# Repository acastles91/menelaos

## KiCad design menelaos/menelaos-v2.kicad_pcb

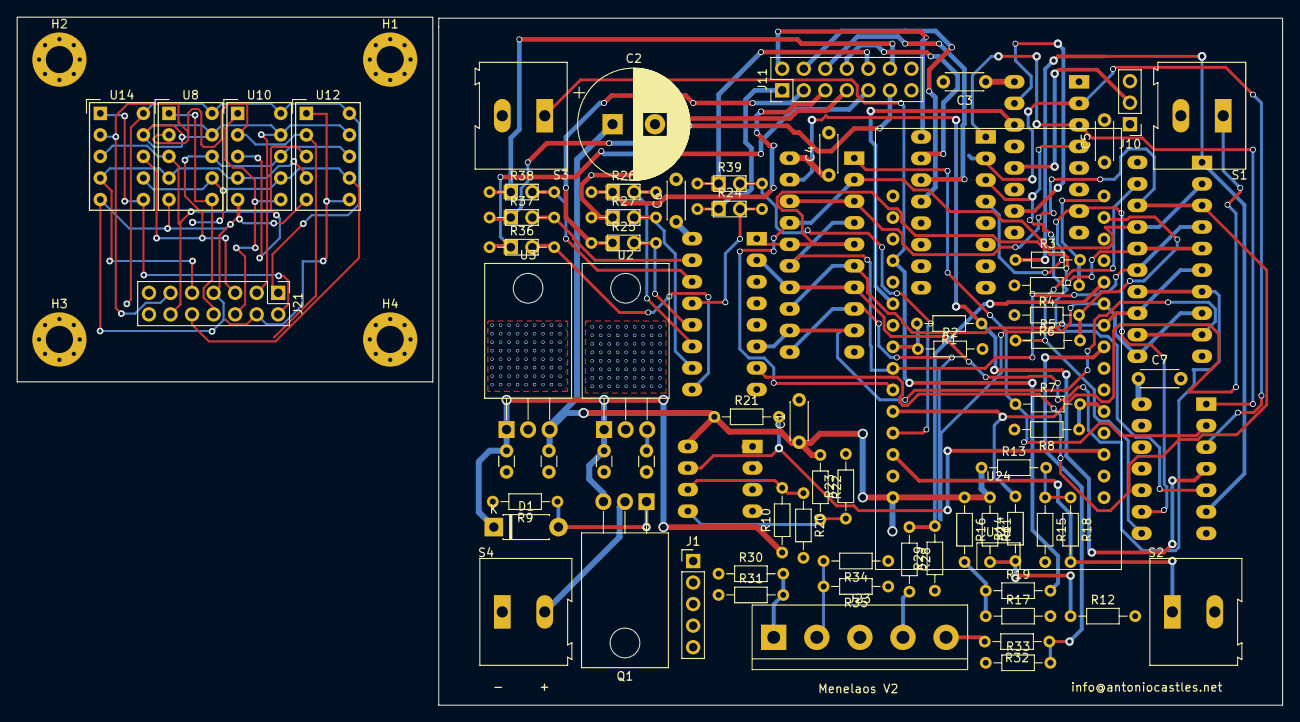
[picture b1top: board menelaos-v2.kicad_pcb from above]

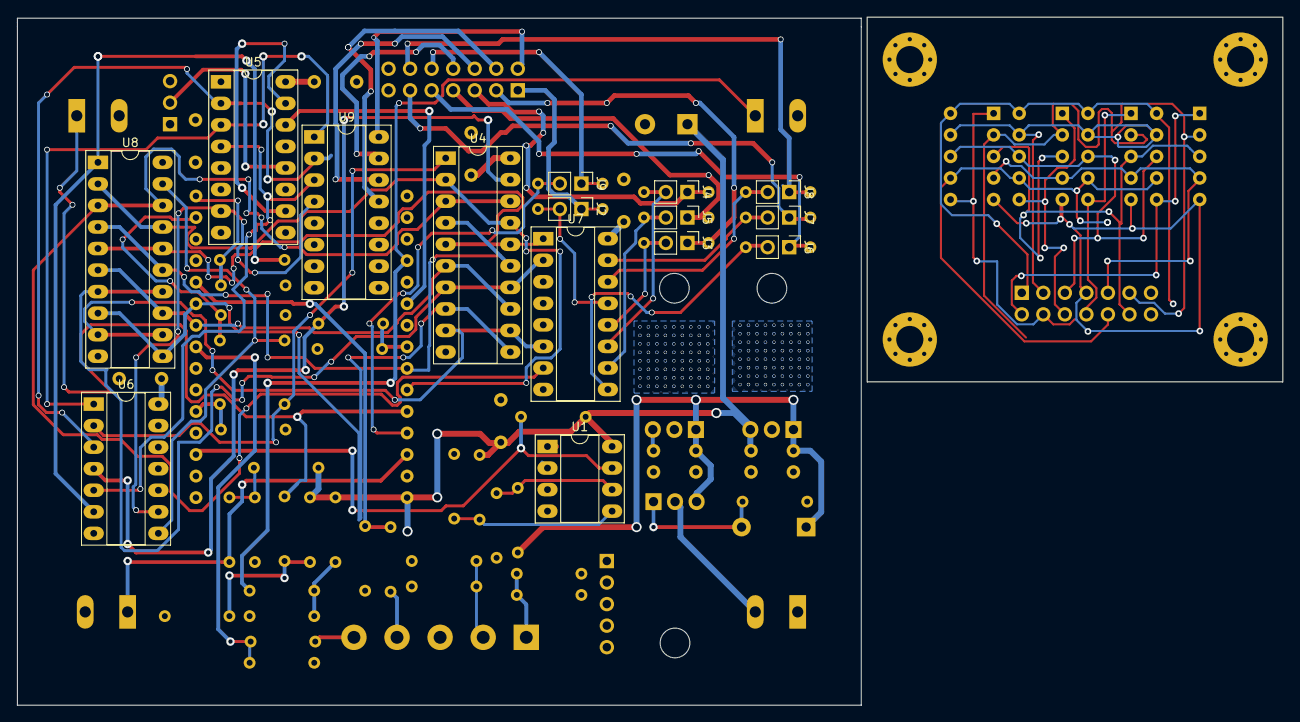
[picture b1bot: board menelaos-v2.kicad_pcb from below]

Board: 4 copper layers, 149.2 x 81.1 mm, 87 parts (15 on the bottom side), 64 nets.

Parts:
C1, C3, C4, C5, C6, C7: C; C_Disc_D4.3mm_W1.9mm_P5.00mm
C2: CP1; CP_Radial_D13.0mm_P5.00mm
D1: D_Zener-10V; D_DO-41_SOD81_P7.62mm_Horizontal
H1, H2, H3, H4: MountingHole; MountingHole_3.2mm_M3_Pad_Via
J1: Conn_01x05_Male; PinHeader_1x05_P2.54mm_Vertical
J2, J3, J4, J5, J6, J7, J8, J9: Conn_01x02_Male; PinHeader_1x02_P2.54mm_Vertical
J10: Conn_01x03_Male; PinHeader_1x03_P2.54mm_Vertical
J11, J21: Conn_02x07_Counter_Clockwise; PinHeader_2x07_P2.54mm_Vertical-counterclockwise
J23: DIN-5-TerminalBlock; TerminalBlock_bornier-5_P5.08mm
Murata-Ceramic-Capacitor-50v1-22uF1, Murata-Ceramic-Capacitor-50v1-22uF2, Murata-Ceramic-Capacitor-50v1-22uF3, Murata-Ceramic-Capacitor-50v1-22uF4: C; C_Disc_D3.0mm_W1.6mm_P2.50mm
Q1: IRF5305-Reverse-Polarity; TO-220-3_Horizontal_TabDown
R1, R3, R5, R7, R11, R13, R16: 5K; R_Axial_DIN0204_L3.6mm_D1.6mm_P7.62mm_Horizontal
R2, R4, R6, R8, R12, R14, R15, R17, R18, R19: 10K; R_Axial_DIN0204_L3.6mm_D1.6mm_P7.62mm_Horizontal
R9: 100K; R_Axial_DIN0204_L3.6mm_D1.6mm_P7.62mm_Horizontal
R10, R20, R21, R22, R23, R24, R25, R26, R27, R36, R37, R38, R39: R; R_Axial_DIN0204_L3.6mm_D1.6mm_P7.62mm_Horizontal
R28, R32: 50; R_Axial_DIN0204_L3.6mm_D1.6mm_P7.62mm_Horizontal
R29, R30, R33, R34: 220; R_Axial_DIN0204_L3.6mm_D1.6mm_P7.62mm_Horizontal
R31, R35: 100; R_Axial_DIN0204_L3.6mm_D1.6mm_P7.62mm_Horizontal
S1, S2, S3, S4: Generic-Switch; TerminalBlock_Altech_AK300-2_P5.00mm
U1: LM393; DIP-8_W7.62mm_Socket_LongPads
U2, U3: L7805; TO-220-3_Horizontal_TabDown
U4, U8#2: 74HCT244; DIP-20_W7.62mm_Socket_LongPads
U5: 74HC4017E; DIP-16_W7.62mm_Socket_LongPads
U6: 74HC04; DIP-14_W7.62mm_Socket_LongPads
U7: 74HC4511E; DIP-16_W7.62mm_Socket_LongPads
U8, U10, U12, U14: HDSP-7503; HDSP-A151
U9: ULN2003; DIP-16_W7.62mm_Socket_LongPads
U24: ESP32-WROOM-32D; ESP32-DEVKIT

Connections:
+5VL: C1.1, C2.1, Murata-Ceramic-Capacitor-50v1-22uF4.1, R11.1, R13.1, R16.1, R21.1, R22.1, U1.8, U3.3, U24.15
+12V: D1.1, Murata-Ceramic-Capacitor-50v1-22uF1.1, Murata-Ceramic-Capacitor-50v1-22uF2.1, Q1.3, R10.1, U2.1, U3.1
/7-segmet-display/BCD_out1: U4.3, U4.18, U7.7, U8#2.3, U8#2.18
/7-segmet-display/BCD_out2: U4.5, U4.16, U7.1, U8#2.5, U8#2.16
/7-segmet-display/BCD_out3: U4.7, U4.14, U7.2, U8#2.7, U8#2.14
/7-segmet-display/BCD_out4: U4.9, U4.12, U7.6, U8#2.9, U8#2.12
GND: C1.2, C2.2, C3.2, C4.2, C5.2, C6.2, C7.2, J1.1, J1.2, J1.3, J1.4, J1.5, J10.3, Murata-Ceramic-Capacitor-50v1-22uF1.2, Murata-Ceramic-Capacitor-50v1-22uF2.2, Murata-Ceramic-Capacitor-50v1-22uF3.2, Murata-Ceramic-Capacitor-50v1-22uF4.2, R2.2, R4.2, R6.2, R8.2, R9.2, R12.2, R15.2, R17.2, R20.2, R23.2, R29.1, R30.1, R31.1, R33.1, R34.1, R35.1, S1.2, S2.2, S3.2, S4.1, U1.4, U2.2, U3.2, U4.10, U5.8, U5.13, U6.7, U7.5, U7.8, U8#2.10, U9.8, U24.14, U24.17
unnamed: D1.2, Q1.1, R9.1
unnamed: J10.2, U5.12
unnamed: Q1.2, S4.2
unnamed: R10.2, R20.1, U1.6
unnamed: R11.2, R12.1, R14.1
unnamed: R13.2, R15.1, R18.1
unnamed: R16.2, R17.1, R19.1
unnamed: R22.2, R23.1, U1.5
unnamed: U5.2, U6.3, U9.2
unnamed: U5.3, U6.1, U9.1
unnamed: U5.4, U6.5, U9.3
unnamed: U5.7, U6.9, U9.4
unnamed: U5.10, U5.15
_a: J2.1, J11.1, R24.1
_a1: U4.2, U4.17, U8#2.2, U8#2.17, U24.10
_a2: U4.4, U4.15, U8#2.4, U8#2.15, U24.9
_a3: U4.6, U4.13, U8#2.6, U8#2.13, U24.24
_a4: U4.8, U4.11, U8#2.8, U8#2.11, U24.25
_b: J3.1, J11.2, R25.1
_c: J4.1, J11.3, R26.1
_chA: R28.1, R29.2, U24.26
_chB: R32.1, R33.2, U24.23
_clk: U5.14, U24.6
_config: R19.2, S3.1, U24.4
_d: J5.1, J11.4, R27.1
_dp: J9.1, J11.10, R39.1
_dpBoard: J9.2, R39.2, U24.12
_e: J6.1, J11.5, R36.1
_f: J7.1, J11.6, R37.1
_g: J8.1, J11.9, R38.1
_hundreds: R5.1, U6.8, U8#2.19
_hundredsBoard: R5.2, R6.1, U24.29
_mode: R18.2, S2.1, U24.13
_ones: R1.1, U4.19, U6.4
_onesBoard: R1.2, R2.1, U24.8
_save: R21.2, U1.7, U24.18
_tens: R3.1, U6.6, U8#2.1
_tensBoard: R3.2, R4.1, U24.30
_thousands: R7.1, U4.1, U6.2
_thousandsBoard: R7.2, R8.1, U24.20
_zero: R14.2, S1.1, U24.11
a: J2.2, R24.2, U7.13
b: J3.2, R25.2, U7.12
black: J23.5, R32.2
blue: C3.1, C4.1, C5.1, C6.1, C7.1, J10.1, J23.3, Murata-Ceramic-Capacitor-50v1-22uF3.1, U2.3, U4.20, U5.16, U6.14, U7.3, U7.4, U7.16, U8#2.20
c: J4.2, R26.2, U7.11
d: J5.2, R27.2, U7.10
e: J6.2, R36.2, U7.9
f: J7.2, R37.2, U7.15
g: J8.2, R38.2, U7.14
hundreds: J11.13, U9.13
ones: J11.11, U9.15
red: J23.1, R30.2, R31.2
tens: J11.12, U9.14
thousands: J11.14, U9.16
white: J23.2, R34.2, R35.2
yellow: J23.4, R28.2

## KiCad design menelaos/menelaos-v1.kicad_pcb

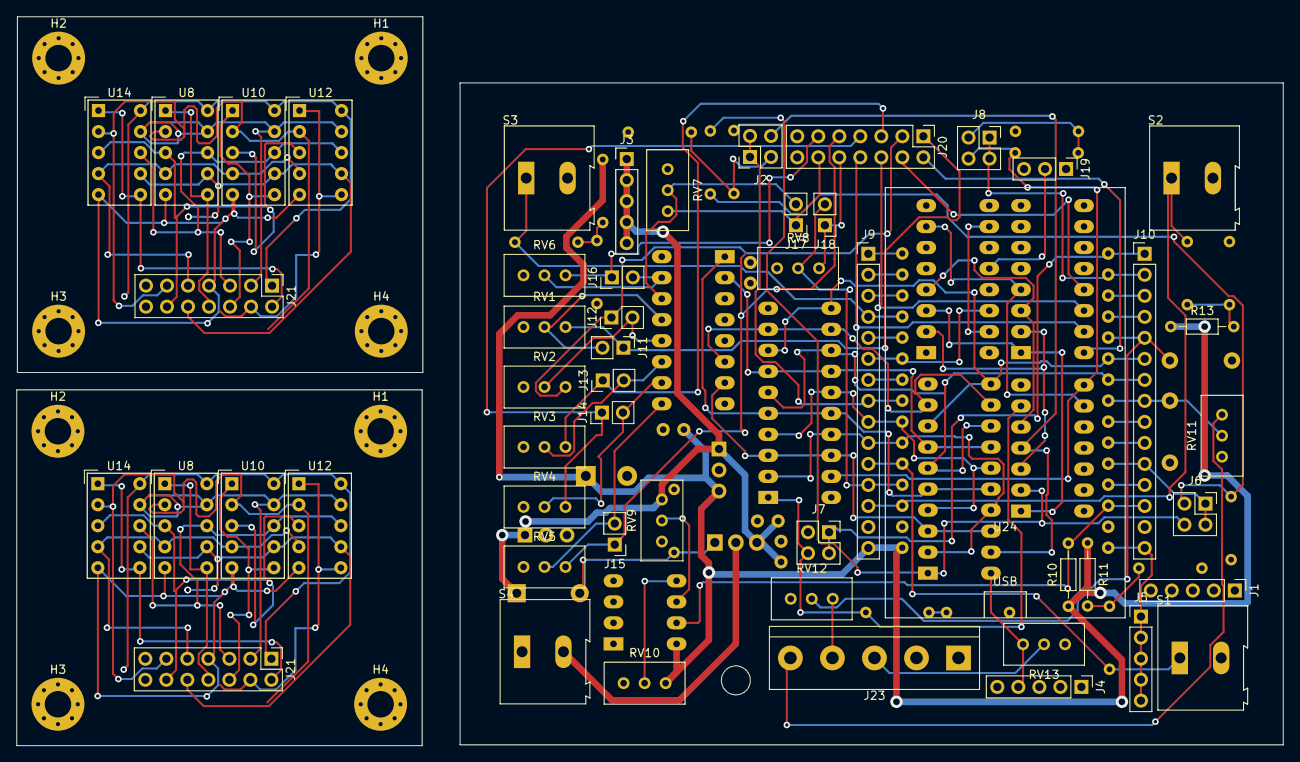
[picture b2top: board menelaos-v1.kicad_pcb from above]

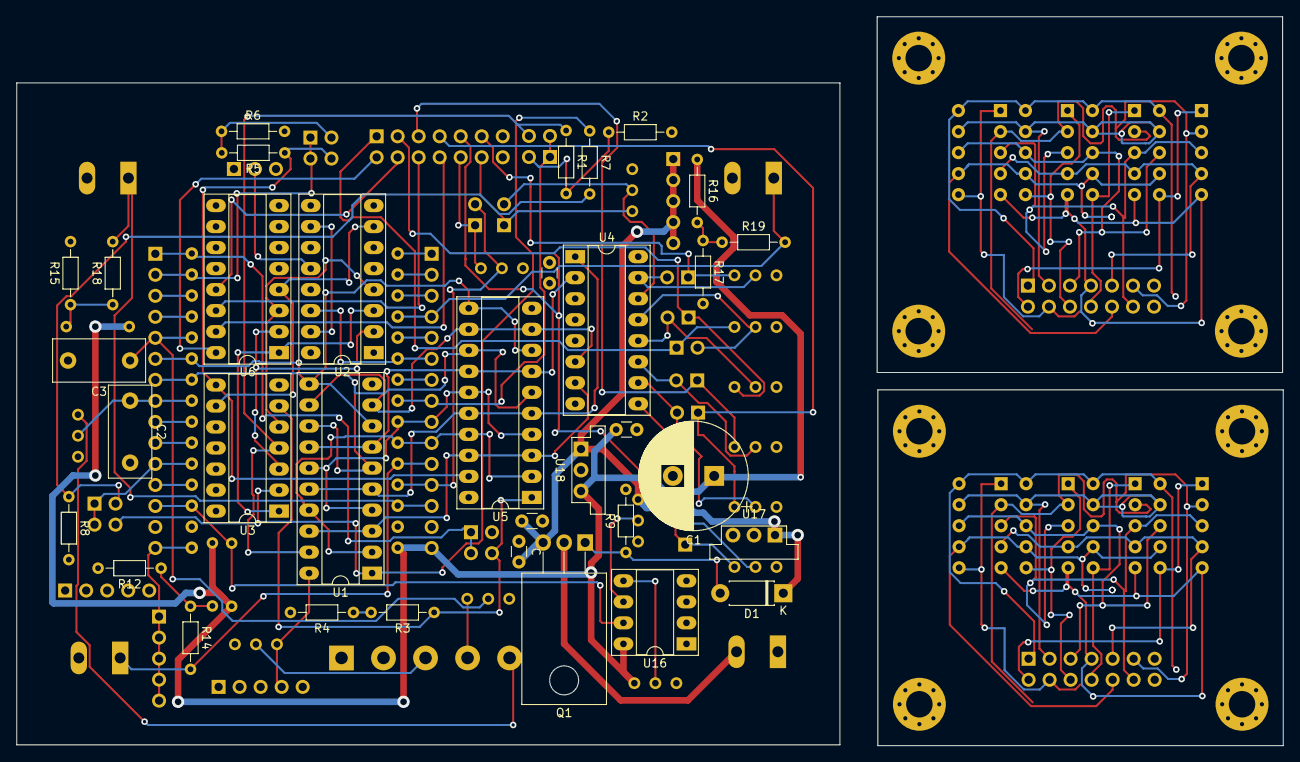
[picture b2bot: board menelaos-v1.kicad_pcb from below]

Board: 4 copper layers, 99.5 x 80.0 mm, 94 parts (34 on the bottom side), 90 nets.

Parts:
C1: CP1; CP_Radial_D13.0mm_P5.00mm
C2, C3: C; C_Disc_D11.0mm_W5.0mm_P7.50mm
D1: D_Zener-10V; D_DO-41_SOD81_P7.62mm_Horizontal
H1, H1#2, H2, H2#2, H3, H3#2, H4, H4#2: MountingHole; MountingHole_3.2mm_M3_Pad_Via
J1, J3, J4, J5: Conn_01x05_Male; PinHeader_1x05_P2.54mm_Vertical
J2, J6, J7, J8: Conn_02x02_Counter_Clockwise; PinSocket_2x02_P2.54mm_Vertical_CounterClockWise
J9, J10: Conn_01x15_Male; PinHeader_1x15_P2.54mm_Vertical
J11, J12, J13, J14, J15, J16, J17, J18: Conn_01x02_Male; PinHeader_1x02_P2.54mm_Vertical
J19: Conn_01x03_Male; PinHeader_1x03_P2.54mm_Vertical
J20, J21, J21#2: Conn_02x07_Counter_Clockwise; PinHeader_2x07_P2.54mm_Vertical-counterclockwise
J23: DIN-5-TerminalBlock; TerminalBlock_bornier-5_P5.08mm
Murata-Ceramic-Capacitor-50v1-22uF1, Murata-Ceramic-Capacitor-50v1-22uF2, Murata-Ceramic-Capacitor-50v1-22uF3, Murata-Ceramic-Capacitor-50v1-22uF4: C; C_Disc_D3.0mm_W1.6mm_P2.50mm
Q1: IRF5305-Reverse-Polarity; TO-220-3_Horizontal_TabDown
R1, R3, R5, R7, R11, R13, R16: 5K; R_Axial_DIN0204_L3.6mm_D1.6mm_P7.62mm_Horizontal
R2, R4, R6, R8, R12, R14, R15, R17, R18, R19: 10K; R_Axial_DIN0204_L3.6mm_D1.6mm_P7.62mm_Horizontal
R9: 100K; R_Axial_DIN0204_L3.6mm_D1.6mm_P7.62mm_Horizontal
R10: R; R_Axial_DIN0204_L3.6mm_D1.6mm_P7.62mm_Horizontal
RV1, RV2, RV3, RV4, RV5, RV6, RV7, RV8, RV9, RV10, RV11, RV12, RV13: R_POT_TRIM; Potentiometer_Bourns_3296W_Vertical
S1, S2, S3, S4: Generic-Switch; TerminalBlock_Altech_AK300-2_P5.00mm
U1, U5: 74HCT244; DIP-20_W7.62mm_Socket_LongPads
U2: 74HC4017E; DIP-16_W7.62mm_Socket_LongPads
U3: 74HC04; DIP-14_W7.62mm_Socket_LongPads
U4: 74HC4511E; DIP-16_W7.62mm_Socket_LongPads
U6: ULN2003; DIP-16_W7.62mm_Socket_LongPads
U8, U8#2, U10, U10#2, U12, U12#2, U14, U14#2: HDSP-7503; HDSP-A151
U16: LM393; DIP-8_W7.62mm_Socket_LongPads
U17, U18: OKI-78SR-5v; Converter_DCDC_muRata_OKI-78SR_Vertical
U24: ESP32-WROOM-32D; ESP32-DEVKIT

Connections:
+3V3: J5.1, J5.2, J5.3, J5.4, J5.5, J10.15, U24.16
+5VL: C1.1, J9.15, Murata-Ceramic-Capacitor-50v1-22uF4.1, R10.1, R11.1, R13.1, R16.1, RV10.1, U16.8, U18.3, U24.15
+5VP: J4.1, J4.2, J4.3, J4.4, J4.5, J19.1, Murata-Ceramic-Capacitor-50v1-22uF3.1, RV13.1, U1.20, U2.16, U3.14, U4.3, U4.4, U4.16, U5.20, U17.3
+12V: D1.1, J3.1, J3.2, J3.3, J3.4, J3.5, Murata-Ceramic-Capacitor-50v1-22uF1.1, Murata-Ceramic-Capacitor-50v1-22uF2.1, Q1.3, RV9.1, U17.1, U18.1
+a: J21#2.1, U8#2.10, U10#2.10, U12#2.10, U14#2.10
+b: J21#2.2, U8#2.9, U10#2.9, U12#2.9, U14#2.9
+c: J21#2.3, U8#2.8, U10#2.8, U12#2.8, U14#2.8
+d: J21#2.4, U8#2.5, U10#2.5, U12#2.5, U14#2.5
+dp: J21#2.10, U8#2.7, U10#2.7, U12#2.7, U14#2.7
+e: J21#2.5, U8#2.4, U10#2.4, U12#2.4, U14#2.4
+f: J21#2.6, U8#2.2, U10#2.2, U12#2.2, U14#2.2
+g: J21#2.9, U8#2.3, U10#2.3, U12#2.3, U14#2.3
+hundreds: J21#2.13, U12#2.1, U12#2.6
+ones: J21#2.11, U8#2.1, U8#2.6
+tens: J21#2.12, U10#2.1, U10#2.6
+thousands: J21#2.14, U14#2.1, U14#2.6
/7-segmet-display/BCD_out1: U1.3, U1.18, U4.7, U5.3, U5.18
/7-segmet-display/BCD_out2: U1.5, U1.16, U4.1, U5.5, U5.16
/7-segmet-display/BCD_out3: U1.7, U1.14, U4.2, U5.7, U5.14
/7-segmet-display/BCD_out4: U1.9, U1.12, U4.6, U5.9, U5.12
unnamed: D1.2, Q1.1, R9.1
unnamed: J9.1, U24.1
unnamed: J9.2, U24.2
unnamed: J9.3, U24.3
unnamed: J9.5, U24.5
unnamed: J9.7, U24.7
unnamed: J10.3, U24.28
unnamed: J10.4, U24.27
unnamed: J10.9, U24.22
unnamed: J10.10, U24.21
unnamed: J10.12, U24.19
unnamed: J19.2, U2.12
unnamed: R11.2, R12.1, R14.1
unnamed: R13.2, R15.1, R18.1
unnamed: R16.2, R17.1, R19.1
unnamed: RV9.2, U16.6
unnamed: RV10.2, U16.5
unnamed: U2.2, U3.3, U6.2
unnamed: U2.3, U3.1, U6.1
unnamed: U2.4, U3.5, U6.3
unnamed: U2.7, U3.9, U6.4
unnamed: U2.10, U2.15
POWER-IN+: Q1.2, S4.2
POWER-IN-: C1.2, C2.2, C3.2, J1.1, J1.2, J1.3, J1.4, J1.5, J9.14, J10.14, J19.3, J23.1, J23.2, Murata-Ceramic-Capacitor-50v1-22uF1.2, Murata-Ceramic-Capacitor-50v1-22uF2.2, Murata-Ceramic-Capacitor-50v1-22uF3.2, Murata-Ceramic-Capacitor-50v1-22uF4.2, R2.2, R4.2, R6.2, R8.2, R9.2, R12.2, R15.2, R17.2, RV1.3, RV2.3, RV3.3, RV4.3, RV5.3, RV6.3, RV7.3, RV8.3, RV9.3, RV10.3, RV11.3, RV12.3, RV13.3, S1.2, S2.2, S3.2, S4.1, U1.10, U2.8, U2.13, U3.7, U4.5, U4.8, U5.10, U6.8, U16.4, U17.2, U18.2, U24.14, U24.17
_a: J11.1, J20.1, RV1.1
_a1: J9.10, U1.2, U1.17, U5.2, U5.17, U24.10
_a2: J9.9, U1.4, U1.15, U5.4, U5.15, U24.9
_a3: J10.7, U1.6, U1.13, U5.6, U5.13, U24.24
_a4: J10.6, U1.8, U1.11, U5.8, U5.11, U24.25
_b: J12.1, J20.2, RV2.1
_c: J13.1, J20.3, RV3.1
_chA: C3.1, J10.5, RV12.2, U24.26
_chB: C2.1, J10.8, RV11.2, U24.23
_clk: J9.6, U2.14, U24.6
_config: J9.4, R19.2, S3.1, U24.4
_d: J14.1, J20.4, RV4.1
_dp: J18.1, J20.10, RV8.1
_dpBoard: J9.12, J18.2, RV8.2, U24.12
_e: J15.1, J20.5, RV5.1
_f: J16.1, J20.6, RV6.1
_g: J17.1, J20.9, RV7.1
_hundreds: J8.2, R5.1, U3.8, U5.19
_hundredsBoard: J8.3, J8.4, J10.2, U24.29
_mode: J9.13, R18.2, S2.1, U24.13
_ones: J2.2, R1.1, U1.19, U3.4
_onesBoard: J2.3, J2.4, J9.8, U24.8
_save: J10.13, R10.2, U16.7, U24.18
_tens: J7.2, R3.1, U3.6, U5.1
_tensBoard: J7.3, J7.4, J10.1, U24.30
_thousands: J6.2, R7.1, U1.1, U3.2
_thousandsBoard: J6.3, J6.4, J10.11, U24.20
_zero: J9.11, R14.2, S1.1, U24.11
a: J11.2, RV1.2, U4.13
b: J12.2, RV2.2, U4.12
c: J13.2, RV3.2, U4.11
d: J14.2, RV4.2, U4.10
e: J15.2, RV5.2, U4.9
f: J16.2, RV6.2, U4.15
g: J17.2, RV7.2, U4.14
gray: J23.5, RV11.1
hundreds: J20.13, U6.13
hundreds33: J8.1, R5.2, R6.1
ones: J20.11, U6.15
ones33: J2.1, R1.2, R2.1
tens: J20.12, U6.14
tens33: R3.2, R4.1
thousands: J20.14, U6.16
thousands33: J6.1, R7.2, R8.1
white: J23.3, RV13.2
yellow: J23.4, RV12.1

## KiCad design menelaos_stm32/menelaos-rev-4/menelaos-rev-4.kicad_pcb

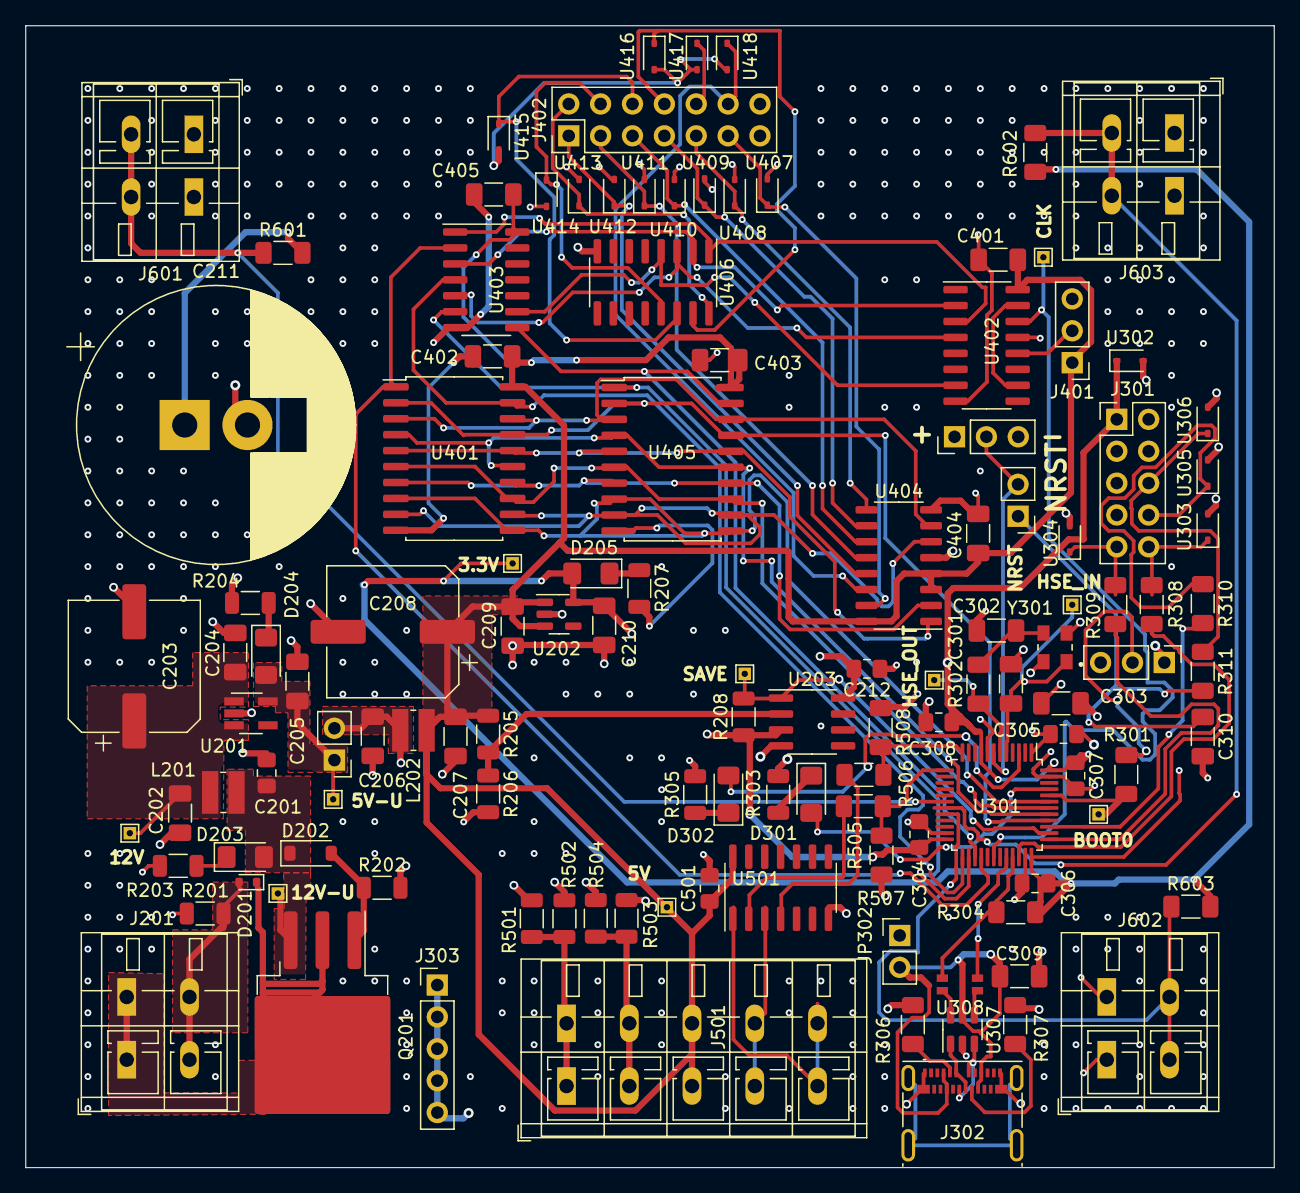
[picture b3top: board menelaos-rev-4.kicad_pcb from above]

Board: 4 copper layers, 99.5 x 91.0 mm, 124 parts (0 on the bottom side), 84 nets.

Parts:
C201, C212: 0.1uF; C_0805_2012Metric_Pad1.18x1.45mm_HandSolder
C202, C205, C206, C207, C404: 0.1uF; C_1206_3216Metric_Pad1.33x1.80mm_HandSolder
C203, C208: C_Polarized; CP_Elec_10x12.6
C204: 0.33uF; C_1206_3216Metric_Pad1.33x1.80mm_HandSolder
C209, C210: 1uF; C_1206_3216Metric_Pad1.33x1.80mm_HandSolder
C211: CP1; CP_Radial_D22.0mm_P5.00mm_SnapIn
C301, C302: 12p; C_1206_3216Metric_Pad1.33x1.80mm_HandSolder
C303: 10u; C_1206_3216Metric_Pad1.33x1.80mm_HandSolder
C304, C305, C306, C307, C308: 100n; C_0805_2012Metric_Pad1.18x1.45mm_HandSolder
C309: 10p; C_1206_3216Metric_Pad1.33x1.80mm_HandSolder
C310: 100n; C_1206_3216Metric_Pad1.33x1.80mm_HandSolder
C401, C402, C403, C405: C; C_1206_3216Metric_Pad1.33x1.80mm_HandSolder
C501: C; C_0805_2012Metric_Pad1.18x1.45mm_HandSolder
D201: ESD5Zxx; D_SOD-523
D202: D_Zener-10V; D_SOD-123
D203, D204, D205, D301, D302: LED; LED_1206_3216Metric_Pad1.42x1.75mm_HandSolder
J201, J601, J602, J603: Screw_Terminal_01x02; TerminalBlock_WAGO_236-402_1x02_P5.00mm_45Degree
J301: Conn_02x05_Counter_Clockwise; PinHeader_2x05_P2.54mm_Vertical
J302: USB_C_Receptacle_USB2.0; USB_C_Receptacle_Molex_105450-0101
J303: Conn_01x05_Male; PinHeader_1x05_P2.54mm_Vertical
J401: Conn_01x03_Male; PinHeader_1x03_P2.54mm_Vertical
J402: Conn_02x07_Counter_Clockwise; PinHeader_2x07_P2.54mm_Vertical-CounterClockWise
J501: DIN-5-TerminalBlock; TerminalBlock_WAGO_236-405_1x05_P5.00mm_45Degree
JP201, JP302: Jumper_2_Open; PinHeader_1x02_P2.54mm_Vertical
JP301, JP304: Jumper_3_Open; PinHeader_1x03_P2.54mm_Vertical
JP303: Jumper_2_Bridged; PinHeader_1x02_P2.54mm_Vertical
L201, L202: L; L_Wuerth_MAPI-3015
Q201: IRF5305-Reverse-Polarity; TO-263-3_TabPin2
R201: 0; R_1206_3216Metric
R202: 100K; R_1206_3216Metric
R203, R204: R_US; R_1206_3216Metric
R205: 5K; R_1206_3216Metric
R206: 10K; R_1206_3216Metric
R207, R303, R305: R100; R_1206_3216Metric
R208: R; R_1206_3216Metric
R301, R505, R506, R507, R508, R601, R602, R603: R10k; R_1206_3216Metric_Pad1.30x1.75mm_HandSolder
R302: R0; R_1206_3216Metric_Pad1.30x1.75mm_HandSolder
R304: R1k5; R_1206_3216Metric_Pad1.30x1.75mm_HandSolder
R306, R307: R5k1; R_1206_3216Metric_Pad1.30x1.75mm_HandSolder
R308, R309, R310, R311: 49R9; R_1206_3216Metric_Pad1.30x1.75mm_HandSolder
R501, R503: 220; R_1206_3216Metric
R502, R504: 100; R_1206_3216Metric
TP201, TP202, TP203, TP204, TP205, TP206, TP301, TP302, TP303, TP401: TestPoint; TestPoint_THTPad_1.0x1.0mm_Drill0.5mm
U201: NCP718-LDO_Regulator; SOT-23-5_HandSoldering
U202: MIC5504-3.3YM5; SOT-23-5
U203: LM2903; SOIC-8_3.9x4.9mm_P1.27mm
U301: STM32F103CBTx; LQFP-48_7x7mm_P0.5mm
U302, U303, U304, U305, U306, U407, U408, U409, U410, U411, U412, U413, U414, U415, U416, U417, U418: PESD3V3L1BA-Bidirectional_Diode; D_SOD-323
U307: USBLC6-2SC6; SOT-23-6
U308: SRF3216A-Common_Mode_Choke; Bourns_SRF3216A
U401, U405: 74HCT244; SOIC-20W_7.5x12.8mm_P1.27mm
U402: 74HC4017E; SOIC-16_3.9x9.9mm_P1.27mm
U403: 74HC04; SOIC-14_3.9x8.7mm_P1.27mm
U404: 74HC4511E; SO-16_3.9x9.9mm_P1.27mm
U406: ULN2003; SOIC-16_3.9x9.9mm_P1.27mm
U501: 74HC14; SOIC-14_3.9x8.7mm_P1.27mm
Y301: CX3225SB16000H0PSTC1-Crystal; OSCCC320X250X60N

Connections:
+3.3V: C210.1, C211.1, C212.2, C303.1, C304.1, C305.1, C306.1, C307.1, C308.1, D205.2 (A), J301.1, JP301.3 (B), JP304.1 (A), R208.1, R304.2, R601.2, R602.2, R603.2, TP206.1, U202.5 (VOUT), U203.3 (+), U203.8 (V+), U301.1 (VBAT), U301.9 (VDDA), U301.24 (VDD), U301.36 (VDD), U301.48 (VDD), U302.1
+12V: C202.1, C203.1, C204.1, L201.2, TP202.1, U201.1 (Vin), U201.3 (EN)
/cable/SCHMITT_A: R506.1, U501.4
/cable/SCHMITT_B: R505.1, U501.2
/mcu/BOOT0: R301.2, TP303.1, U301.44 (BOOT0)
/mcu/BOOT_JUMPER: JP301.2 (C), R301.1
/mcu/CONN_NRST: J301.6, R311.1, U306.1
/mcu/CONN_SWCLK: J301.9, R309.1, U304.1
/mcu/CONN_SWDIO: J301.10, R308.1, U303.1
/mcu/CONN_SWO: J301.8, R310.1, U305.1
/mcu/HSE_IN: C301.1, TP301.1, U301.5 (PD0), Y301.1
/mcu/HSE_OUT: R302.1, TP302.1, U301.6 (PD1)
/mcu/JUMPER_NRST: C310.1, JP303.1 (A), R311.2
/mcu/MCU_LED1: D301.2 (A), U301.45 (PB8)
/mcu/MCU_LED1-K: D301.1 (K), R303.1
/mcu/MCU_LED2: D302.2 (A), U301.3 (PC14)
/mcu/MCU_LED2-K: D302.1 (K), R305.1
/mcu/MCU_NRST: JP303.2 (B), JP304.2 (C), U301.7 (NRST)
/mcu/MCU_SWCLK: R309.2, U301.37 (PA14)
/mcu/MCU_SWDIO: R308.2, U301.34 (PA13)
/mcu/MCU_SWO: R310.2, U301.39 (PB3)
/mcu/USB_CMC_D+: U307.6 (I/O1), U308.3
/mcu/USB_CMC_D-: U307.4 (I/O2), U308.4
/mcu/USB_CONN_CC1: J302.A5 (CC1), R306.2
/mcu/USB_CONN_CC2: J302.B5 (CC2), R307.2
/mcu/USB_CONN_D+: J302.A6 (D+), J302.B6 (D+), U307.1 (I/O1)
/mcu/USB_CONN_D-: J302.A7 (D-), J302.B7 (D-), U307.3 (I/O2)
/mcu/USB_D+: R304.1, U301.33 (PA12), U308.2
/mcu/USB_D-: U301.32 (PA11), U308.1
/mcu/XTAL_IN: C302.1, R302.2, Y301.3
/power/5V-Jumper: C205.1, D204.2 (A), JP201.1 (A), TP203.1, U201.5 (Vout)
/power/12V-Unfiltered: C201.1, D202.1 (K), D203.2 (A), L201.1, Q201.3 (S), TP201.1
/power/12V-Unfiltered__LED_K: D203.1 (K), R203.2
/power/LDO2_LED_K: D205.1 (K), R207.1
/power/LDO_LED_K: D204.1 (K), R204.2
/power/POL-FET-D: D201.1 (K), J201.1, Q201.2 (D)
/power/POL-FET-G: D202.2 (A), Q201.1 (G), R202.1
/power/PowerIn-: D201.2 (A), J201.2, R201.2
/power/V-REF: R205.2, R206.1, U203.2 (-)
/seven-segment-display/4017_RST: U402.10 (4), U402.15 (MASTER_RESET)
/seven-segment-display/4017_TC: J401.2, U402.12 (TERMINAL_COUNT)
/seven-segment-display/BCD_out1: U401.3 (2Y0), U401.18 (1Y0), U404.7 (D0), U405.3 (2Y0), U405.18 (1Y0)
/seven-segment-display/BCD_out2: U401.5 (2Y1), U401.16 (1Y1), U404.1 (D1), U405.5 (2Y1), U405.16 (1Y1)
/seven-segment-display/BCD_out3: U401.7 (2Y2), U401.14 (1Y2), U404.2 (D2), U405.7 (2Y2), U405.14 (1Y2)
/seven-segment-display/BCD_out4: U401.9 (2Y3), U401.12 (1Y3), U404.6 (D3), U405.9 (2Y3), U405.12 (1Y3)
/seven-segment-display/COUNT_0: U402.3 (0), U403.1, U406.1 (I1)
/seven-segment-display/COUNT_1: U402.2 (1), U403.3, U406.2 (I2)
/seven-segment-display/COUNT_2: U402.4 (2), U403.5, U406.3 (I3)
/seven-segment-display/COUNT_3: U402.7 (3), U403.9, U406.4 (I4)
GND: C201.2, C202.2, C203.2, C204.2, C205.2, C206.2, C207.2, C208.2, C209.2, C210.2, C211.2, C212.1, C301.2, C302.2, C303.2, C304.2, C305.2, C306.2, C307.2, C308.2, C309.1, C310.2, C401.2, C402.2, C403.2, C404.2, C405.2, C501.2, J301.2, J301.3, J301.5, J302.A1 (GND), J302.A12 (GND), J302.B1 (GND), J302.B12 (GND), J303.1, J303.2, J303.3, J303.4, J303.5, J401.3, J601.1, J602.1, J603.1, JP301.1 (A), JP304.3 (B), R201.1, R202.2, R203.1, R204.1, R206.2, R207.2, R303.2, R305.2, R306.1, R307.1, R501.1, R502.1, R503.1, R504.1, R507.1, R508.1, U201.2 (GND), U202.2 (GND), U203.4 (V-), U301.8 (VSSA), U301.23 (VSS), U301.35 (VSS), U301.47 (VSS), U302.2, U303.2, U304.2, U305.2, U306.2, U307.2 (GND), U401.10 (GND), U402.8 (GND), U402.13 (CLOCK_ENABLE), U403.7 (GND), U404.5 (LE), U404.8 (GND), U405.10 (GND), U406.8 (GND), U407.2, U408.2, U409.2, U410.2, U411.2, U412.2, U413.2, U414.2, U415.2, U416.2, U417.2, U418.2, U501.7 (GND), Y301.2 (GND), Y301.4 (GND__1)
Unfiltered_5V: C206.1, JP201.2 (B), JP302.1 (A), L202.1
VBUS: C309.2, J302.A4 (VBUS), J302.A9 (VBUS), J302.B4 (VBUS), J302.B9 (VBUS), JP302.2 (B), U307.5 (VBUS)
_a1: U301.40 (PB4), U401.2 (1A0), U401.17 (2A0), U405.2 (1A0), U405.17 (2A0)
_a2: U301.41 (PB5), U401.4 (1A1), U401.15 (2A1), U405.4 (1A1), U405.15 (2A1)
_a3: U301.42 (PB6), U401.6 (1A2), U401.13 (2A2), U405.6 (1A2), U405.13 (2A2)
_a4: U301.43 (PB7), U401.8 (1A3), U401.11 (2A3), U405.8 (1A3), U405.11 (2A3)
_chA: R506.2, R508.2, U301.12 (PA2)
_chB: R505.2, R507.2, U301.13 (PA3)
_clk: TP401.1, U301.30 (PA9), U402.14 (CLOCK)
_config: J603.2, R602.1, U301.19 (PB1)
_hundreds: U301.27 (PB14), U403.8, U405.19 (2OE)
_mode: J602.2, R603.1, U301.20 (PB2)
_ones: U301.25 (PB12), U401.19 (2OE), U403.4
_save: R208.2, TP205.1, U203.1, U301.38 (PA15)
_tens: U301.26 (PB13), U403.6, U405.1 (1OE)
_thousands: U301.28 (PB15), U401.1 (1OE), U403.2
_zero: J601.2, R601.1, U301.18 (PB0)
a: J402.1, U404.13 (a), U412.1
b: J402.2, U404.12 (b), U411.1
black: J501.5, U501.1
blue: C207.1, C208.1, C209.1, C401.1, C402.1, C403.1, C404.1, C405.1, C501.1, J401.1, J501.3, L202.2, R205.1, TP204.1, U202.1 (VIN), U202.3 (EN), U401.20 (VCC), U402.16 (Vcc), U403.14 (VCC), U404.3 (LT), U404.4 (BL), U404.16 (VCC), U405.20 (VCC), U501.14 (VCC)
c: J402.3, U404.11 (c), U410.1
d: J402.4, U404.10 (d), U409.1
dp: J402.10, U417.1
e: J402.5, U404.9 (e), U408.1
f: J402.6, U404.15 (f), U407.1
g: J402.9, U404.14 (g), U418.1
hundreds: J402.13, U406.13 (O4), U414.1
ones: J402.11, U406.15 (O2), U416.1
red: J501.1, R501.2, R502.2
tens: J402.12, U406.14 (O3), U415.1
thousands: J402.14, U406.16 (O1), U413.1
white: J501.2, R503.2, R504.2
yellow: J501.4, U501.3

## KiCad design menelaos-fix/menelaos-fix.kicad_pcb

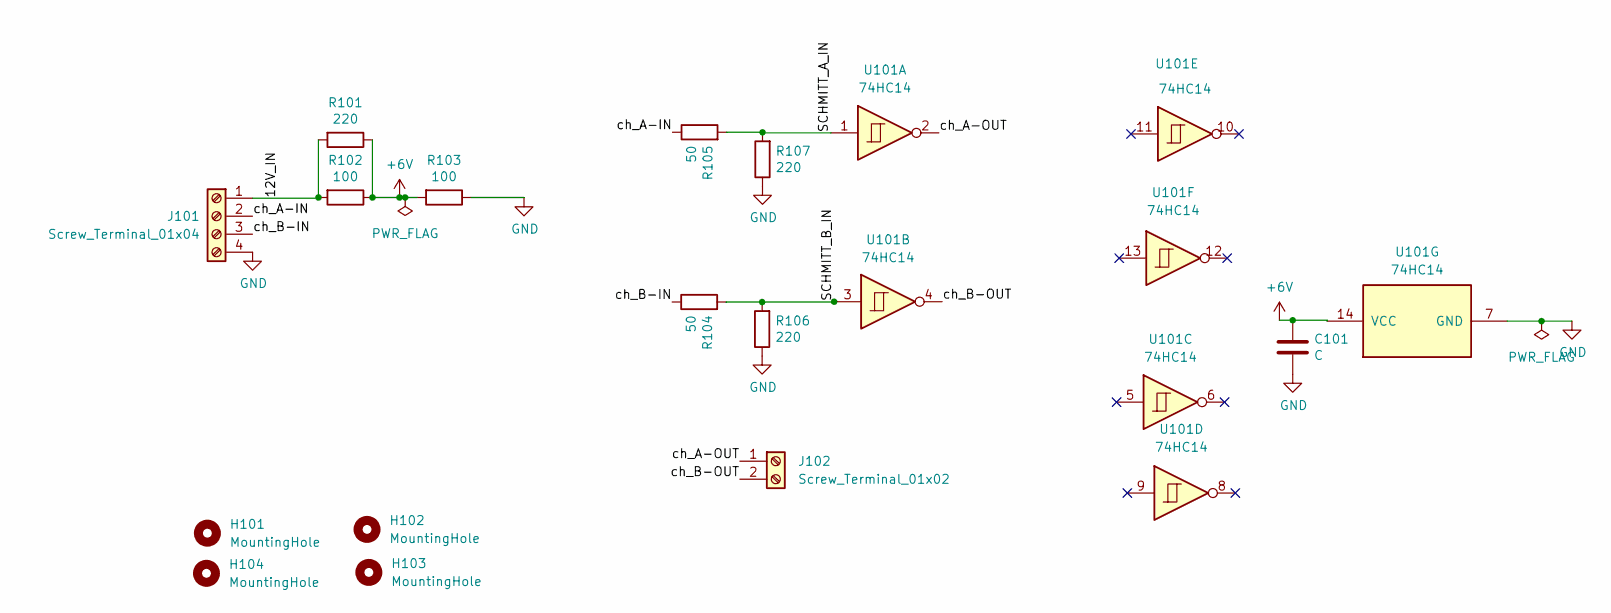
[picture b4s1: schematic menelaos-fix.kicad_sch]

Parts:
C101: C; C_Disc_D3.0mm_W1.6mm_P2.50mm
H101, H102, H103, H104: MountingHole; MountingHole_4.3mm_M4
J101: Screw_Terminal_01x04; TerminalBlock_Altech_AK300-4_P5.00mm
J102: Screw_Terminal_01x02; TerminalBlock_Altech_AK300-2_P5.00mm
R101, R106, R107: 220; R_Axial_DIN0204_L3.6mm_D1.6mm_P7.62mm_Horizontal
R102, R103: 100; R_Axial_DIN0204_L3.6mm_D1.6mm_P7.62mm_Horizontal
R104, R105: 50; R_Axial_DIN0204_L3.6mm_D1.6mm_P7.62mm_Horizontal
U101: 74HC14; DIP-14_W7.62mm_Socket; Digikey_PN 296-1643-5-ND

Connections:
+6V: C101.1, R101.1, R102.1, R103.2, U101.14 (VCC)
/12V_IN: J101.1, R101.2, R102.2
/SCHMITT_A_IN: R105.2, R107.2, U101.1
/SCHMITT_B_IN: R104.2, R106.2, U101.3
/ch_A-IN: J101.2, R105.1
/ch_A-OUT: J102.1, U101.2
/ch_B-IN: J101.3, R104.1
/ch_B-OUT: J102.2, U101.4
GND: C101.2, J101.4, R103.1, R106.1, R107.1, U101.7 (GND)

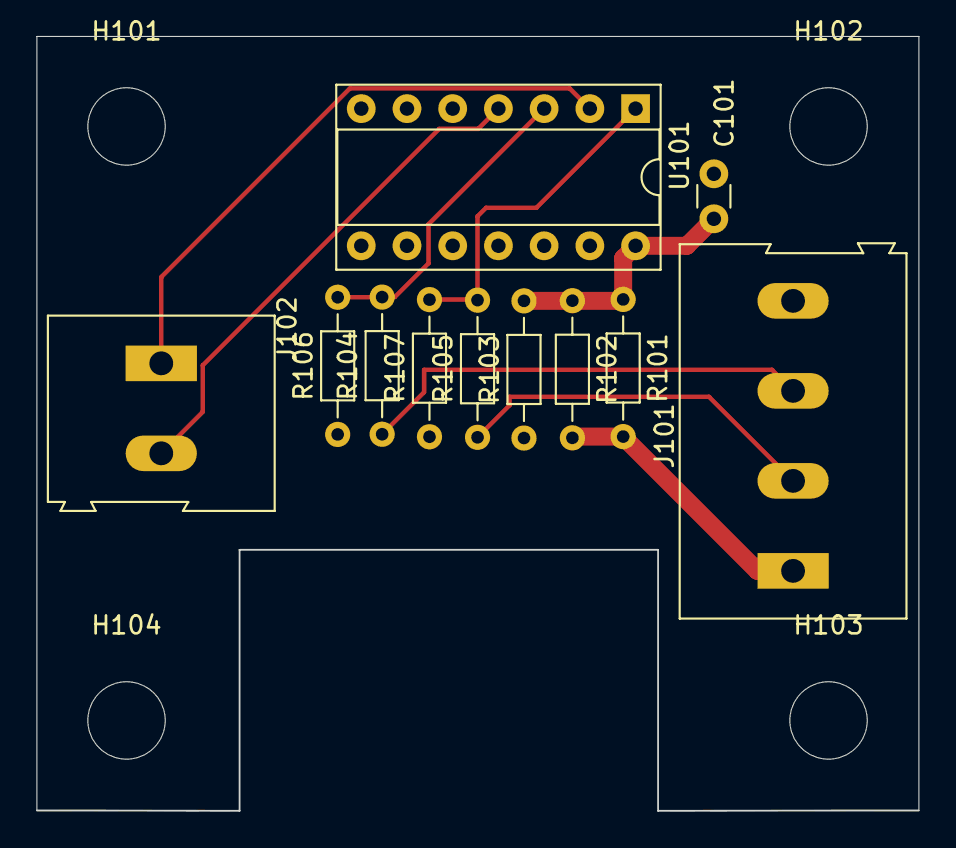
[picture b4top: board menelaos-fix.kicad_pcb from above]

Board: 2 copper layers, 49.0 x 43.0 mm, 15 parts (0 on the bottom side), 9 nets.

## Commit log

2021-11-03 menelaos before v2
2021-11-27 This is the delivered version. Both the KiCad project and the code are what was delivered to UdK
2022-01-25 apparently fixed sleep bug
2022-01-26 Previous commit still presented the problem. In this one I introduced an Idle mode, which happens during saving in shutdown. After waking up from sleep the program enters into an infinite loop in thi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
2023-01-28 Salwa is in Freiburg. Fake number solution
2024-06-01 before chat gpt intervention
2024-06-01 After chat gpt improvements
